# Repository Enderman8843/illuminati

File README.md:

# Illuminati

## Why did I build this 
I built this drafting triangle to improve my routing skills as well using the render feature , which I hadn't used yet also this scale has Wi-Fi and an inbuilt accelerometer which would allow the user to level

## Features 
* WiFi and Bluetooth 
* Inch and MM scale 
* Accelerometer 
* RGB LEDs 
* User-Assigned GPIO Switches 

## How to Use this 
First connect this device via usb-c cable to your pc then download MicroPython from https://micropython.org/download/RPI_PICO/ then download the python firmware file in `Firmware` then put it in the root of the pico folder that will appear if Micropython is successfull , Then the led will blink

*Note the firmware is untested

## PCB Layout

| PCB Layout | Schematic / Wiring |
| :---: | :---: |
|  |  |

## PCB Render

| Front | Rear |
| :---: | :---: |
|  |  |

## Case

---

## BOM

| Item | Description | Quantity | Unit Price ($) | Total Price ($) | URL |
|------|-------------|----------|----------------|-----------------|-----|
| PCB+PCBA | Custom PCB Manufacturing (JLCPCB) | 1 | 73| 73 | https://jlcpcb.com |
| Case | 3D Printed Case (Will be Printed Myself) | 1 | 0.00 | 0.00 | https://hackclub.com |
| **TOTAL** |  |  |  | **73.00** |  |

## BOM PCBA 

| Comment | Designator | Footprint | LCSC | Quantity |
| :--- | :--- | :--- | :--- | ---: |
| 100nF | C1, C10, C12, C13, C15, C16, C17, C18, C19, C20, C22, C24, C25, C3, C5, C6 | C_0402_1005Metric | C1525 | 16 |
| 10k | R11, R3, R9 | R_0402_1005Metric | C11616 | 3 |
| 10uF | C4, C7 | C_0402_1005Metric | C15525 | 2 |
| 10uF | C23 | C_0603_1608Metric | C1691 | 1 |
| 10uF | C2 | C_0402_1005Metric | C15525 | 1 |
| 1K | R1, R10, R4 | R_0402_1005Metric | C11702 | 3 |
| 1N5819WS | D1 | D_SOD-323 | C2921026 | 1 |
| 22pF | C11, C9 | C_0402_1005Metric | C1555 | 2 |
| 22uF | C8 | C_0402_1005Metric | C105226 | 1 |
| 4.7k | R12, R13 | R_0402_1005Metric | C11663 | 2 |
| 470 | R2, R8 | R_0402_1005Metric | C25117 | 2 |
| 5k1 | R5, R6 | R_0402_1005Metric | C105873 | 2 |
| AP2112K-3.3 | U4 | SOT-23-5 | C23380830 | 1 |
| LED_PWR | D4 | LED_0603_1608Metric | C2287 | 1 |
| LED_USR | D5 | LED_0603_1608Metric | C2287 | 1 |
| LIS3DH | U6 | LGA-16_3x3mm_P0.5mm_LayoutBorder3x5y | C15134 | 1 |
| SW_Push | SW1 | KEY-SMD_4P-L4.7-W3.5-P1.70-LS5.5 | C2915174 | 1 |
| SW_RST | SW2 | KEY-SMD_4P-L4.7-W3.5-P1.70-LS5.5 | C2915174 | 1 |
| USB_C_Receptacle_USB2.0_14P | J2 | USB_C_Receptacle_GCT_USB4105-xx-A_16P_TopMnt_Horizontal | C183603 | 1 |
| W25Q32JVSSIQ_C179173 | U2 | SOIC-8_L5.3-W5.3-P1.27-LS8.0-BL | C179173 | 1 |
| X322512MSB4SI | X1 | Crystal_SMD_3225-4Pin_3.2x2.5mm | C9002 | 1 |
| USBLC6-2SC6 | U5 | SOT-23-6 |  | 1 |

## JLCPCB

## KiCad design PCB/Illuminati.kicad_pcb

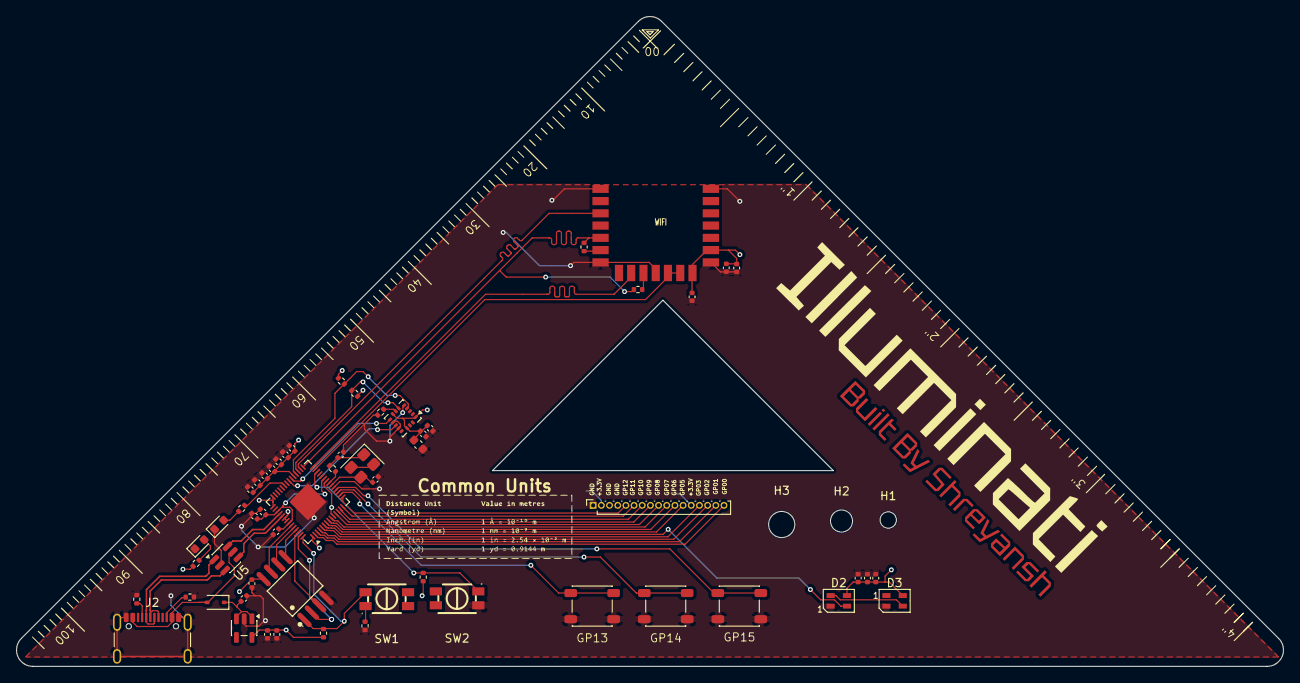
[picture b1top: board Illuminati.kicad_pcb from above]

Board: 2 copper layers, 155.0 x 79.5 mm, 61 parts (1 on the bottom side), 53 nets.

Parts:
C1, C3, C5, C6, C10, C12, C13, C15, C16, C17, C18, C19, C20, C22, C24, C25: 100nF; C_0402_1005Metric
C2: 10uf; C_0402_1005Metric
C4, C7: 10uF; C_0402_1005Metric
C8: 22uf; C_0402_1005Metric
C9, C11: 22pF; C_0402_1005Metric
C14, C21: 1uF; C_0402_1005Metric
C23: 10uF; C_0603_1608Metric
D1: 1N5819WS; D_SOD-323
D2, D3: SK6805; LED_SK6805_PLCC4_2.4x2.7mm_P1.3mm
D4: LED_PWR; LED_0603_1608Metric
D5: LED_USR; LED_0603_1608Metric
G: LOGO
H1: MountingHole; MountingHole_2mm
H2: MountingHole; MountingHole_2.7mm_M2.5
H3: MountingHole; MountingHole_3.2mm_M3
J1: Conn_01x17_Socket; PinSocket_1x17_P1.00mm_Vertical
J2: USB_C_Receptacle_USB2.0_14P; USB_C_Receptacle_GCT_USB4105-xx-A_16P_TopMnt_Horizontal
R1, R4, R10: 1K; R_0402_1005Metric
R2, R8: 470; R_0402_1005Metric
R3, R9, R11: 10k; R_0402_1005Metric
R5, R6: 5k1; R_0402_1005Metric
R7: 330R; R_0402_1005Metric
R12, R13: 4.7k; R_0402_1005Metric
SW1: SW_Push; KEY-SMD_4P-L4.7-W3.5-P1.70-LS5.5
SW2: SW_RST; KEY-SMD_4P-L4.7-W3.5-P1.70-LS5.5
SW3, SW4, SW5: SW_Push; SW_SPST_PTS647_Sx38
U1: RP2040; QFN-56-1EP_7x7mm_P0.4mm_EP3.2x3.2mm
U2: W25Q32JVSSIQ_C179173; SOIC-8_L5.3-W5.3-P1.27-LS8.0-BL
U3: Radio Module; rpi_rmc20452t
U4: AP2112K-3.3; SOT-23-5
U5: USBLC6-2SC6; SOT-23-6
U6: LIS3DH; LGA-16_3x3mm_P0.5mm_LayoutBorder3x5y
X1: X322512MSB4SI; Crystal_SMD_3225-4Pin_3.2x2.5mm

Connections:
+1V1: C12.1, C13.1, C14.1, U1.23 (DVDD), U1.45 (VREG_VOUT), U1.50 (DVDD)
+3.3V: C1.1, C2.2, C3.2, C4.1, C5.2, C6.1, C8.2, C10.2, C15.1, C16.1, C17.1, C18.1, C19.1, C20.1, C21.1, C22.1, C23.1, C24.1, C25.1, D2.4 (VDD), D3.4 (VDD), J1.2, J1.13, R2.1, R3.2, R4.2, R12.1, R13.1, U1.1 (IOVDD), U1.10 (IOVDD), U1.22 (IOVDD), U1.33 (IOVDD), U1.42 (IOVDD), U1.43 (ADC_AVDD), U1.44 (VREG_IN), U1.48 (USB_VDD), U1.49 (IOVDD), U2.8 (VCC), U3.14 (VDDIO), U3.16 (VIN), U4.5 (VOUT), U6.1 (VDD_IO), U6.8 (CS), U6.14 (VDD)
+5V: C7.1, D1.1 (K), U4.1 (VIN), U4.3 (EN)
/GP0: J1.17, U1.2 (GPIO0)
/GP1: J1.16, U1.3 (GPIO1)
/GP2: J1.15, U1.4 (GPIO2)
/GP3: J1.14, U1.5 (GPIO3)
/GP4: D2.3 (DIN), U1.6 (GPIO4)
/GP5: J1.12, U1.7 (GPIO5)
/GP6: J1.11, U1.8 (GPIO6)
/GP7: J1.10, U1.9 (GPIO7)
/GP8: J1.9, U1.11 (GPIO8)
/GP9: J1.8, U1.12 (GPIO9)
/GP10: J1.7, U1.13 (GPIO10)
/GP11: J1.6, U1.14 (GPIO11)
/GP12: J1.5, U1.15 (GPIO12)
/GP13: SW4.2, U1.16 (GPIO13)
/GP14: SW5.2, U1.17 (GPIO14)
/GP15: SW3.2, U1.18 (GPIO15)
/GP16: U1.27 (GPIO16), U3.12 (WL_ON), U3.13 (BT_ON)
/GP17: U1.28 (GPIO17), U3.9 (CS)
/GP18: R8.1, R9.1, U1.29 (GPIO18), U3.5 (DI)
/GP19: U1.30 (GPIO19), U3.3 (SCLK)
/GP20: R12.2, U1.31 (GPIO20), U6.6 (SDI)
/GP21: R13.2, U1.32 (GPIO21), U6.4 (SPC)
/GP22: U1.34 (GPIO22), U6.9 (INT2)
/GP23: U1.35 (GPIO23), U6.11 (INT1)
/GP25: R7.1, U1.37 (GPIO25)
GND: C1.2, C2.1, C3.1, C4.2, C5.1, C6.2, C7.2, C8.1, C9.1, C10.1, C11.2, C12.2, C13.2, C14.2, C15.2, C16.2, C17.2, C18.2, C19.2, C20.2, C21.2, C22.2, C23.2, C24.2, C25.2, D2.2 (VSS), D3.2 (VSS), D4.1 (K), D5.1 (K), J1.1, J1.3, J1.4, J2.A1 (GND), J2.A12 (GND), J2.B1 (GND), J2.B12 (GND), J2.SH (SHIELD), R1.1, R5.2, R6.2, R11.2, SW2.2, SW3.1, SW4.1, SW5.1, U1.19 (TESTEN), U1.57 (GND), U2.4 (GND), U3.1 (GND), U3.7 (GND), U3.11 (GND), U3.15 (GND), U3.21 (GND), U4.2 (GND), U5.2 (GND), U6.5 (GND), U6.10 (GND), U6.12 (GND), X1.2, X1.4
unnamed: C11.1, R10.1, X1.1
unnamed: D2.1 (DOUT), D3.3 (DIN)
unnamed: D4.2 (A), R2.2
unnamed: D5.2 (A), R7.2
unnamed: J2.A5 (CC1), R5.1
unnamed: J2.B5 (CC2), R6.1
unnamed: R1.2, SW1.1
unnamed: R8.2, U3.6 (DO)
unnamed: R9.2, U3.10 (nIRQ)
unnamed: R11.1, U6.7 (SDO)
RUN: R4.1, SW2.1, U1.26 (RUN)
SPI_CLK: U1.52 (QSPI_SCLK), U2.6 (CLK)
SPI_CS: R3.1, SW1.2, U1.56 (QSPI_SS), U2.1 (~CS)
SPI_SD0: U1.53 (QSPI_SD0), U2.5 (DI(IO0))
SPI_SD1: U1.55 (QSPI_SD1), U2.2 (DO(IO1))
SPI_SD2: U1.54 (QSPI_SD2), U2.3 (WP#(IO2))
SPI_SD3: U1.51 (QSPI_SD3), U2.7 (HOLD#orRESET#(IO3))
USB_CLEAN_D_N: U1.46 (USB_DM), U5.6 (I/O1)
USB_CLEAN_D_P: U1.47 (USB_DP), U5.4 (I/O2)
USB_D_N: J2.A7 (D-), J2.B7 (D-), U5.1 (I/O1)
USB_D_P: J2.A6 (D+), J2.B6 (D+), U5.3 (I/O2)
VBUS: D1.2 (A), J2.A4 (VBUS), J2.A9 (VBUS), J2.B4 (VBUS), J2.B9 (VBUS), U5.5 (VBUS)
XIN: C9.2, U1.20 (XIN), X1.3
XOUT: R10.2, U1.21 (XOUT)

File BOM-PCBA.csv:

Comment,Designator,Footprint,LCSC,Quantity
100nF,"C1,C10,C12,C13,C15,C16,C17,C18,C19,C20,C22,C24,C25,C3,C5,C6",C_0402_1005Metric,C1525,16
10k,"R11,R3,R9",R_0402_1005Metric,C11616,3
10uF,"C4,C7",C_0402_1005Metric,C15525,2
10uF,C23,C_0603_1608Metric,C1691,1
10uf,C2,C_0402_1005Metric,C15525,1
1K,"R1,R10,R4",R_0402_1005Metric,C11702,3
1N5819WS,D1,D_SOD-323,C2921026,1
22pF,"C11,C9",C_0402_1005Metric,C1555,2
22uf,C8,C_0402_1005Metric,C105226,1
4.7k,"R12,R13",R_0402_1005Metric,C11663,2
470,"R2,R8",R_0402_1005Metric,C25117,2
5k1,"R5,R6",R_0402_1005Metric,C105873,2
AP2112K-3.3,U4,SOT-23-5,C23380830,1
LED_PWR,D4,LED_0603_1608Metric,C2287,1
LED_USR,D5,LED_0603_1608Metric,C2287,1
LIS3DH,U6,LGA-16_3x3mm_P0.5mm_LayoutBorder3x5y,C15134,1
SW_Push,SW1,KEY-SMD_4P-L4.7-W3.5-P1.70-LS5.5,C2915174,1
SW_RST,SW2,KEY-SMD_4P-L4.7-W3.5-P1.70-LS5.5,C2915174,1
USB_C_Receptacle_USB2.0_14P,J2,USB_C_Receptacle_GCT_USB4105-xx-A_16P_TopMnt_Horizontal,C183603,1
W25Q32JVSSIQ_C179173,U2,SOIC-8_L5.3-W5.3-P1.27-LS8.0-BL,C179173,1
X322512MSB4SI,X1,Crystal_SMD_3225-4Pin_3.2x2.5mm,C9002,1
1uF,C21,C_0402_1005Metric,,1
SK6805,D3,LED_SK6805_PLCC4_2.4x2.7mm_P1.3mm,,1
RP2040,U1,QFN-56-1EP_7x7mm_P0.4mm_EP3.2x3.2mm,,1
SW_Push,SW4,SW_SPST_PTS647_Sx38,,1
Radio Module,U3,rpi_rmc20452t,,1
330R,R7,R_0402_1005Metric,,1
SK6805,D2,LED_SK6805_PLCC4_2.4x2.7mm_P1.3mm,,1
Conn_01x17_Socket,J1,PinSocket_1x17_P1.00mm_Vertical,,1
SW_Push,SW5,SW_SPST_PTS647_Sx38,,1
1uF,C14,C_0402_1005Metric,,1
SW_Push,SW3,SW_SPST_PTS647_Sx38,,1
USBLC6-2SC6,U5,SOT-23-6,,1
